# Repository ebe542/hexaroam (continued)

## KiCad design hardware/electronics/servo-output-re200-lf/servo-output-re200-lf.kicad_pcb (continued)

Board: 2 copper layers, 83 parts (0 on the bottom side), 38 nets, no tracks yet.

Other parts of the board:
BG0, BG1, BG2, BG3, BG4, BG5: GND; TestPoint_THTPad_D2.0mm_Drill1.0mm
BV0, BV1, BV2, BV3, BV4, BV5: /SERVO_VS; TestPoint_THTPad_D2.0mm_Drill1.0mm

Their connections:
/SERVO_VS: BV0.1, BV1.1, BV2.1, BV3.1, BV4.1, BV5.1; also elsewhere on the board
GND: BG0.1, BG1.1, BG2.1, BG3.1, BG4.1, BG5.1; also elsewhere on the board

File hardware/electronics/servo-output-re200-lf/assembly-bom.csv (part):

Reference,Quantity,Value,Population,Notes,Footprint
J101,1,SIGNAL INPUT,Fit first,"Keyed 2x6 IDC; odd signals, even GND; key notch toward small columns",Connector_IDC:IDC-Header_2x06_P2.54mm_Vertical
J102,1,SERVO POWER IN,Fit first,"Reference Phoenix 1715721, 5.08mm; enlarge two holes to 1.3mm; current sizing for six servos remains open","TerminalBlock_Phoenix:TerminalBlock_Phoenix_MKDS-1,5-2-5.08_1x02_P5.08mm_Horizontal"
C100,1,470uF / 35V,Fit first,"Existing: 470uF/35V, D10 x H20mm, leads 5.00mm gently formed to 5.08mm; observe polarity",HexaRoam_Perfboard:CP_Radial_D10.0mm_P5.08mm_HandFormed
TP101,1,SERVO 0 SIGNAL,Fit first,,TestPoint:TestPoint_THTPad_D2.0mm_Drill1.0mm
TP102,1,LOCAL GND,Fit first,,TestPoint:TestPoint_THTPad_D2.0mm_Drill1.0mm
R101,1,4.7k,Fit first,"Metal film >=0.25W, body fits DIN0207 6.3x2.5mm, P10.16mm",Resistor_THT:R_Axial_DIN0207_L6.3mm_D2.5mm_P10.16mm_Horizontal
R102,1,1k,Fit first,"Metal film >=0.25W, body fits DIN0207 6.3x2.5mm, P10.16mm",Resistor_THT:R_Axial_DIN0207_L6.3mm_D2.5mm_P10.16mm_Horizontal
R103,1,4.7k,Fit first,"Metal film >=0.25W, body fits DIN0207 6.3x2.5mm, P10.16mm",Resistor_THT:R_Axial_DIN0207_L6.3mm_D2.5mm_P10.16mm_Horizontal
R104,1,1k,Fit first,"Metal film >=0.25W, body fits DIN0207 6.3x2.5mm, P10.16mm",Resistor_THT:R_Axial_DIN0207_L6.3mm_D2.5mm_P10.16mm_Horizontal
R105,1,100k,Fit first,"Metal film >=0.25W, body fits DIN0207 6.3x2.5mm, P10.16mm",Resistor_THT:R_Axial_DIN0207_L6.3mm_D2.5mm_P10.16mm_Horizontal
R106,1,180,Fit first,"Metal film >=0.25W, body fits DIN0207 6.3x2.5mm, P10.16mm",Resistor_THT:R_Axial_DIN0207_L6.3mm_D2.5mm_P10.16mm_Horizontal
R107,1,100k,Fit first,"Metal film >=0.25W, body fits DIN0207 6.3x2.5mm, P10.16mm",Resistor_THT:R_Axial_DIN0207_L6.3mm_D2.5mm_P10.16mm_Horizontal
Q101,1,BC547B,Fit first,"Purchasing reference Diotec BC547B / Reichelt BC 547B DIO; 1=C,2=B,3=E; 2.54mm lead row; verify exact supplied package",Package_TO_SOT_THT:TO-92_Inline_Wide
Q102,1,BC547B,Fit first,"Purchasing reference Diotec BC547B / Reichelt BC 547B DIO; 1=C,2=B,3=E; 2.54mm lead row; verify exact supplied package",Package_TO_SOT_THT:TO-92_Inline_Wide
C101,1,100nF,Fit first,100nF ceramic reference envelope <=5x2.5mm; lead pitch formed to 2.54mm,HexaRoam_Perfboard:C_Disc_D5.0mm_P2.54mm_HandFormed
J110,1,SERVO 0,Fit first,1 signal / 2 positive / 3 GND; verify cable orientation,Connector_PinHeader_2.54mm:PinHeader_1x03_P2.54mm_Vertical
R111,1,4.7k,DNP / future,"Metal film >=0.25W, body fits DIN0207 6.3x2.5mm, P10.16mm",Resistor_THT:R_Axial_DIN0207_L6.3mm_D2.5mm_P10.16mm_Horizontal
R112,1,1k,DNP / future,"Metal film >=0.25W, body fits DIN0207 6.3x2.5mm, P10.16mm",Resistor_THT:R_Axial_DIN0207_L6.3mm_D2.5mm_P10.16mm_Horizontal
R113,1,4.7k,DNP / future,"Metal film >=0.25W, body fits DIN0207 6.3x2.5mm, P10.16mm",Resistor_THT:R_Axial_DIN0207_L6.3mm_D2.5mm_P10.16mm_Horizontal
R114,1,1k,DNP / future,"Metal film >=0.25W, body fits DIN0207 6.3x2.5mm, P10.16mm",Resistor_THT:R_Axial_DIN0207_L6.3mm_D2.5mm_P10.16mm_Horizontal
R115,1,100k,DNP / future,"Metal film >=0.25W, body fits DIN0207 6.3x2.5mm, P10.16mm",Resistor_THT:R_Axial_DIN0207_L6.3mm_D2.5mm_P10.16mm_Horizontal
R116,1,180,DNP / future,"Metal film >=0.25W, body fits DIN0207 6.3x2.5mm, P10.16mm",Resistor_THT:R_Axial_DIN0207_L6.3mm_D2.5mm_P10.16mm_Horizontal
R117,1,100k,DNP / future,"Metal film >=0.25W, body fits DIN0207 6.3x2.5mm, P10.16mm",Resistor_THT:R_Axial_DIN0207_L6.3mm_D2.5mm_P10.16mm_Horizontal
Q103,1,BC547B,DNP / future,"Purchasing reference Diotec BC547B / Reichelt BC 547B DIO; 1=C,2=B,3=E; 2.54mm lead row; verify exact supplied package",Package_TO_SOT_THT:TO-92_Inline_Wide
Q104,1,BC547B,DNP / future,"Purchasing reference Diotec BC547B / Reichelt BC 547B DIO; 1=C,2=B,3=E; 2.54mm lead row; verify exact supplied package",Package_TO_SOT_THT:TO-92_Inline_Wide
C102,1,100nF,DNP / future,100nF ceramic reference envelope <=5x2.5mm; lead pitch formed to 2.54mm,HexaRoam_Perfboard:C_Disc_D5.0mm_P2.54mm_HandFormed
J111,1,SERVO 1,DNP / future,1 signal / 2 positive / 3 GND; verify cable orientation,Connector_PinHeader_2.54mm:PinHeader_1x03_P2.54mm_Vertical
R121,1,4.7k,DNP / future,"Metal film >=0.25W, body fits DIN0207 6.3x2.5mm, P10.16mm",Resistor_THT:R_Axial_DIN0207_L6.3mm_D2.5mm_P10.16mm_Horizontal
R122,1,1k,DNP / future,"Metal film >=0.25W, body fits DIN0207 6.3x2.5mm, P10.16mm",Resistor_THT:R_Axial_DIN0207_L6.3mm_D2.5mm_P10.16mm_Horizontal
R123,1,4.7k,DNP / future,"Metal film >=0.25W, body fits DIN0207 6.3x2.5mm, P10.16mm",Resistor_THT:R_Axial_DIN0207_L6.3mm_D2.5mm_P10.16mm_Horizontal
R124,1,1k,DNP / future,"Metal film >=0.25W, body fits DIN0207 6.3x2.5mm, P10.16mm",Resistor_THT:R_Axial_DIN0207_L6.3mm_D2.5mm_P10.16mm_Horizontal
R125,1,100k,DNP / future,"Metal film >=0.25W, body fits DIN0207 6.3x2.5mm, P10.16mm",Resistor_THT:R_Axial_DIN0207_L6.3mm_D2.5mm_P10.16mm_Horizontal
R126,1,180,DNP / future,"Metal film >=0.25W, body fits DIN0207 6.3x2.5mm, P10.16mm",Resistor_THT:R_Axial_DIN0207_L6.3mm_D2.5mm_P10.16mm_Horizontal
R127,1,100k,DNP / future,"Metal film >=0.25W, body fits DIN0207 6.3x2.5mm, P10.16mm",Resistor_THT:R_Axial_DIN0207_L6.3mm_D2.5mm_P10.16mm_Horizontal
Q105,1,BC547B,DNP / future,"Purchasing reference Diotec BC547B / Reichelt BC 547B DIO; 1=C,2=B,3=E; 2.54mm lead row; verify exact supplied package",Package_TO_SOT_THT:TO-92_Inline_Wide
Q106,1,BC547B,DNP / future,"Purchasing reference Diotec BC547B / Reichelt BC 547B DIO; 1=C,2=B,3=E; 2.54mm lead row; verify exact supplied package",Package_TO_SOT_THT:TO-92_Inline_Wide
C103,1,100nF,DNP / future,100nF ceramic reference envelope <=5x2.5mm; lead pitch formed to 2.54mm,HexaRoam_Perfboard:C_Disc_D5.0mm_P2.54mm_HandFormed
J112,1,SERVO 2,DNP / future,1 signal / 2 positive / 3 GND; verify cable orientation,Connector_PinHeader_2.54mm:PinHeader_1x03_P2.54mm_Vertical
R131,1,4.7k,DNP / future,"Metal film >=0.25W, body fits DIN0207 6.3x2.5mm, P10.16mm",Resistor_THT:R_Axial_DIN0207_L6.3mm_D2.5mm_P10.16mm_Horizontal
R132,1,1k,DNP / future,"Metal film >=0.25W, body fits DIN0207 6.3x2.5mm, P10.16mm",Resistor_THT:R_Axial_DIN0207_L6.3mm_D2.5mm_P10.16mm_Horizontal
R133,1,4.7k,DNP / future,"Metal film >=0.25W, body fits DIN0207 6.3x2.5mm, P10.16mm",Resistor_THT:R_Axial_DIN0207_L6.3mm_D2.5mm_P10.16mm_Horizontal
R134,1,1k,DNP / future,"Metal film >=0.25W, body fits DIN0207 6.3x2.5mm, P10.16mm",Resistor_THT:R_Axial_DIN0207_L6.3mm_D2.5mm_P10.16mm_Horizontal
R135,1,100k,DNP / future,"Metal film >=0.25W, body fits DIN0207 6.3x2.5mm, P10.16mm",Resistor_THT:R_Axial_DIN0207_L6.3mm_D2.5mm_P10.16mm_Horizontal
R136,1,180,DNP / future,"Metal film >=0.25W, body fits DIN0207 6.3x2.5mm, P10.16mm",Resistor_THT:R_Axial_DIN0207_L6.3mm_D2.5mm_P10.16mm_Horizontal
R137,1,100k,DNP / future,"Metal film >=0.25W, body fits DIN0207 6.3x2.5mm, P10.16mm",Resistor_THT:R_Axial_DIN0207_L6.3mm_D2.5mm_P10.16mm_Horizontal
Q107,1,BC547B,DNP / future,"Purchasing reference Diotec BC547B / Reichelt BC 547B DIO; 1=C,2=B,3=E; 2.54mm lead row; verify exact supplied package",Package_TO_SOT_THT:TO-92_Inline_Wide
Q108,1,BC547B,DNP / future,"Purchasing reference Diotec BC547B / Reichelt BC 547B DIO; 1=C,2=B,3=E; 2.54mm lead row; verify exact supplied package",Package_TO_SOT_THT:TO-92_Inline_Wide
C104,1,100nF,DNP / future,100nF ceramic reference envelope <=5x2.5mm; lead pitch formed to 2.54mm,HexaRoam_Perfboard:C_Disc_D5.0mm_P2.54mm_HandFormed
J113,1,SERVO 3,DNP / future,1 signal / 2 positive / 3 GND; verify cable orientation,Connector_PinHeader_2.54mm:PinHeader_1x03_P2.54mm_Vertical
R141,1,4.7k,DNP / future,"Metal film >=0.25W, body fits DIN0207 6.3x2.5mm, P10.16mm",Resistor_THT:R_Axial_DIN0207_L6.3mm_D2.5mm_P10.16mm_Horizontal
R142,1,1k,DNP / future,"Metal film >=0.25W, body fits DIN0207 6.3x2.5mm, P10.16mm",Resistor_THT:R_Axial_DIN0207_L6.3mm_D2.5mm_P10.16mm_Horizontal
R143,1,4.7k,DNP / future,"Metal film >=0.25W, body fits DIN0207 6.3x2.5mm, P10.16mm",Resistor_THT:R_Axial_DIN0207_L6.3mm_D2.5mm_P10.16mm_Horizontal
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
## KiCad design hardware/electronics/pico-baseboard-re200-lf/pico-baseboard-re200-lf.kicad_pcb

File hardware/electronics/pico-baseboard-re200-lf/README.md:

# Pico baseboard on Roth RE200-LF

Revision P1, 2026-10-27: unbuilt placement and hand-wiring proposal for the controller assembly of the [revision C schematic](../pico-servo-system/README.md). This folder contains the Pico baseboard only, not the servo-output module or motor supply.

## Files

- [KiCad board](pico-baseboard-re200-lf.kicad_pcb) and [project](pico-baseboard-re200-lf.kicad_pro).
- [Seven-page assembly PDF](assembly-guide.pdf), A4 landscape, drawn at 1:1.
- [Component-side SVG](placement-top.svg) and [mirrored solder-side SVG](placement-bottom.svg).
- Solder-side wire groups: [ground/power](wiring-ground-power.svg), [port A](wiring-port-a.svg), [port B](wiring-port-b.svg), [port C](wiring-port-c.svg), [UART/expansion](wiring-other.svg). Hover a wire in a browser to highlight it and display its ID/net.
- [Complete wire endpoint list](wiring.csv), [physical pin map](pin-map.csv), [assembly parts](assembly-bom.csv).
- [Layout model](layout-model.json) and [verification record](layout-check.json).

The PDF, SVG and CSV files are a snapshot of the same model as the KiCad board. Moving a footprint in KiCad does not automatically update these documents. Reconcile all views and rerun the connection/geometry review before using a changed layout. Recorded hashes identify the checked snapshot.

## Board, coordinate system and views

Use the existing RE200-LF: FR4, 1.5-mm thickness, single-sided solder pads, 61 columns x 38 rows, 2.54-mm pitch, 2.2-mm pad diameter and nominal 1.0-mm holes. The manufacturer calls it 100 x 160 mm; its drawing dimensions are 160.15 x 100.20 mm. The illustrated first hole is modeled at x=3.89, y=3.07 mm from the drawing's top-left corner. Check actual board tolerances and orientation before relying on edge registration.

All IDs are defined looking at the COMPONENT side, with the copper underneath and the Pico USB facing left:

```text
C01-R01 = first column, first row (top left)
x = 3.89 + (column - 1) * 2.54 mm
y = 3.07 + (row - 1) * 2.54 mm
```

These are our coordinate labels, not a promise that the manufacturer's printed numbering has the same viewing orientation. In the solder-side drawings the board is flipped horizontally, like turning a page: USB is on the right, row 1 remains at the top, column 61 is on the left. Physical hole IDs never change. Do not mirror an already mirrored solder-side PDF again.

Print at Actual size / 100%, with all Fit/Shrink options disabled. Measure the 50-mm scale bar and align three widely separated existing holes with the paper before assembly. The PDF is not an instruction to drill all the existing holes.

## Placement and polarity

| Item | Physical position / orientation |
| --- | --- |
| U1 lower socket | C01..C20, R21; Pico pins 1..20 from left to right |
| U1 upper socket | C01..C20, R14; Pico pins 40..21 from left to right |
| Socket row separation | 17.78 mm; two individual 1x20 female headers |
| J1 | Pin 1 positive: C12-R04; pin 2 GND: C10-R04 |
| D2 | 1N5819 cathode/band (pin 1): C16-R08; anode (pin 2): C20-R08 |
| J2 port A | Pin 1 C53-R04; GP0..GP5 on odd pins; even pins GND |
| J3 port B | Pin 1 C53-R15; GP6..GP11 on odd pins; even pins GND |
| J4 port C | Pin 1 C53-R26; GP12..GP17 on odd pins; even pins GND |
| IDC key notches | Face toward the Pico/odd-pin side, left in component view, right in solder view |
| J5 UART | Pins 1..3 C06..C08, R32: TX / RX / GND; 3.3-V TTL |
| J6 expansion | Pins 1..8 C24..C31, R33: GP18, GP19, GP22, GP26, GP27, GP28, 3V3, GND |
| TP1 / TP2 | VSYS: C24-R06 / USB VBUS: C24-R10 |
| TP3 / TP4 / TP5 | GP0: C03-R26 / GP1: C07-R26 / GND: C12-R26 |

Confirm the molded pin-1 mark and key of the actual IDC connectors; pin numbers, not drawing resemblance, define the wiring. Standard footprint body dimensions are reference envelopes. The actual sockets, IDC cable plugs/latches and terminal must fit without contacting the Pico or neighboring parts. Preserve access above USB, BOOTSEL and the Pico SWD pads.

## Mechanical changes on the existing board

The reference J1 is a Phoenix MKDS 1,5/2-5,08 style footprint, 5.08-mm pitch. Its 0.9-mm square pins require 1.3-mm holes. ONLY its two occupied holes, C12-R04 and C10-R04, need widening for this reference part. Remove burrs, inspect the remaining pad rings and support the terminal body when tightening wires. A different terminal needs a fresh pin-size/body check; 5.00-mm pitch is not 5.08 mm. The matching reference part is Phoenix Contact 1715721, listed at Reichelt as MKDS 1,5 2 5,08. A different seller's compatible part still needs a dimension check.

D2 uses the existing 1.0-mm perfboard holes in this layout; verify that the delivered diode leads fit freely. The generic manufacturing footprint's larger drill allowance is not a requirement to force or automatically re-drill the board.

Optional M3 mounting reserves are C03-R03, C59-R03, C03-R36 and C59-R36. Circles show 3.2-mm holes and a 4-mm-radius keep-clear area; they are drawing guides, not existing holes. Decide spacer/washer arrangement and drill only if needed. Keep all nearby pads unused, inspect for damaged copper and leave wiring clear of mounting hardware. The schematic does not determine chassis-hole requirements.

## Hand wiring

All 61 entries in wiring.csv are separate insulated-wire connections. Each row gives component pin and physical hole at both ends. straight_mm is the geometric endpoint distance; cut_hint_mm is that distance plus approximately 20 mm, rounded up, not a measured routed length. Select a practical path and provide enough slack without obstructing sockets or mounting points.

Lines crossing in the SVG/PDF or Cmts.User layer do NOT form junctions. Do not reproduce crossings using bare wire. Only the named endpoints are electrically joined. Solder wire ends to the rear pad/component tail rather than attempting to push several wires through a hole already occupied by a connector pin. No pad has more than three wire ends in the proposed tree; check the real joint can be made cleanly and supported.

Use appropriately sized insulated hookup wire and protect it from sharp leads; keep power/ground mechanically secure. Each IDC's six ground pins are connected. The board carries Pico power and logic only: NO servo-positive rail or motor return current runs through it.

The exported KiCad 10 schematic includes all seven physical Pico GND pins (3, 8, 13, 18, 23, 28, 38). All seven are wired to the common baseboard ground, so the ground network is complete even with the Pico removed. AGND/pin 33, RUN, ADC_VREF and 3V3_EN are not externally wired. Grey pads identify the unused pins.

## Using the KiCad board

Open the .kicad_pcb directly, or use the separate project. The original three-sheet schematic models three physical assemblies, so do not blindly run Update PCB from Schematic from that full system into this controller-only board. There is no duplicated schematic in this folder.

- F.Fab / F.SilkS show component bodies/reference marks.
- Dwgs.User shows the existing perfboard grid, coordinates and optional mounting reserves.
- Cmts.User shows endpoint guide segments for insulated wires. Hide it for a clean placement view.
- There are NO copper tracks or routed jumpers. Ratsnest/unconnected indications are expected until physical hand wiring; this is not a claim of passing production PCB DRC.

KiCad represents the electrical through-hole component pads using a standard THT model with rings on both copper layers. Those front rings are virtual for this guide. The real RE200-LF is single-sided and not plated through. The thousands of unused solder pads/holes are drawing geometry, not a complete fabrication stackup. Do not order PCBs or drill files from this template. Its purpose is editable placement and hand-wiring documentation for an already manufactured board.

The local HexaRoam_Perfboard.pretty footprint retains only the 40 main THT pads of the standard Pico module footprint; SMD/castellation and Pico-local mechanical/SWD pads are not carrier socket holes. It models two 1x20 sockets rather than soldering the Pico directly to the baseboard. Its pin numbering matches the Pico module.

## Verification and owner-performed assembly checks

The saved KiCad board was independently reloaded and checked against the fresh revision C schematic netlist: 13 components, 96 physical pins and 61 wires. Every source root-sheet pin maps to exactly one physical hole. All occupied pads lie on the declared grid without overlap, the component envelope rectangles are separated and inside the board, and every connected net has a complete, non-shorting wire tree. Source/export hashes are in layout-check.json. This is document/geometry verification, not firmware testing or a hardware pass.

Suggested manual sequence for the owner:

1. Print at 100% and check registration; dry-fit sockets, diode and connectors. Check polarity/keying. Decide the terminal/mounting drilling before fitting parts.
2. Fit and solder sockets with the Pico removed. Solder the other parts, then work through the ground/power, A, B, C and other wire tables. Keep a paper checklist per wire.
3. With no power, Pico or external cables attached, check every listed connection and inspect for solder bridges. Verify separate positive nets: external +5V reaches only D2 anode; D2 cathode reaches VSYS; VBUS is not wired directly to either positive net. Use diode mode for D2; capacitor/semiconductor behavior after fitting Pico changes simple resistance readings.
4. Check supply polarity and ground arrangement with the existing USB/UART equipment. Insert the Pico only after inspecting the bare baseboard. Bring up external Pico power and verify VSYS; then repeat the established blink/UART/unloaded-signal checks. Servo power remains on the separate power/output assemblies.

## Reference documents and licensing

- [Roth RE200-LF manufacturer drawing, 072025](https://www.roth-elektronik.com/pdf/en_RE200-LF.pdf). An unmodified local copy and its source/hash are archived under ignored local-data/perfboard/; third-party terms apply.
- [Pico datasheet](../../references/raspberry-pi-pico/pico-datasheet.pdf), mechanical dimensions and external VSYS supply.
- [Reference terminal dimensions](https://www.phoenixcontact.com/gb/products/1715721/pdf): MKDS 1,5/2-5,08, 5.08-mm pitch, 0.9x0.9-mm pins, 1.3-mm holes.
- [Reichelt reference terminal listing](https://www.reichelt.com/de/en/shop/product/pcb_terminal_2-pin_spacing_5_08_mm_0_14_-_1_5_mm_-440491), checked 2026-10-27. Manufacturer/distributor PDF downloads returned HTTP 403 during local archiving; the primary dimensions and source links are recorded here and under local-data/perfboard/reference-terminal-notes.md. The Roth board PDF is archived locally.
- Standard footprint geometry comes from the installed KiCad 10.0 libraries. The socketed Pico derivative retains the [KiCad Libraries License and electronic-design exception](https://gitlab.com/kicad/libraries/kicad-footprints/-/blob/master/LICENSE.md). Project-specific placement, wire data and explanatory documents are HexaRoam material under the repository MIT license; upstream footprint and datasheet rights remain separate.

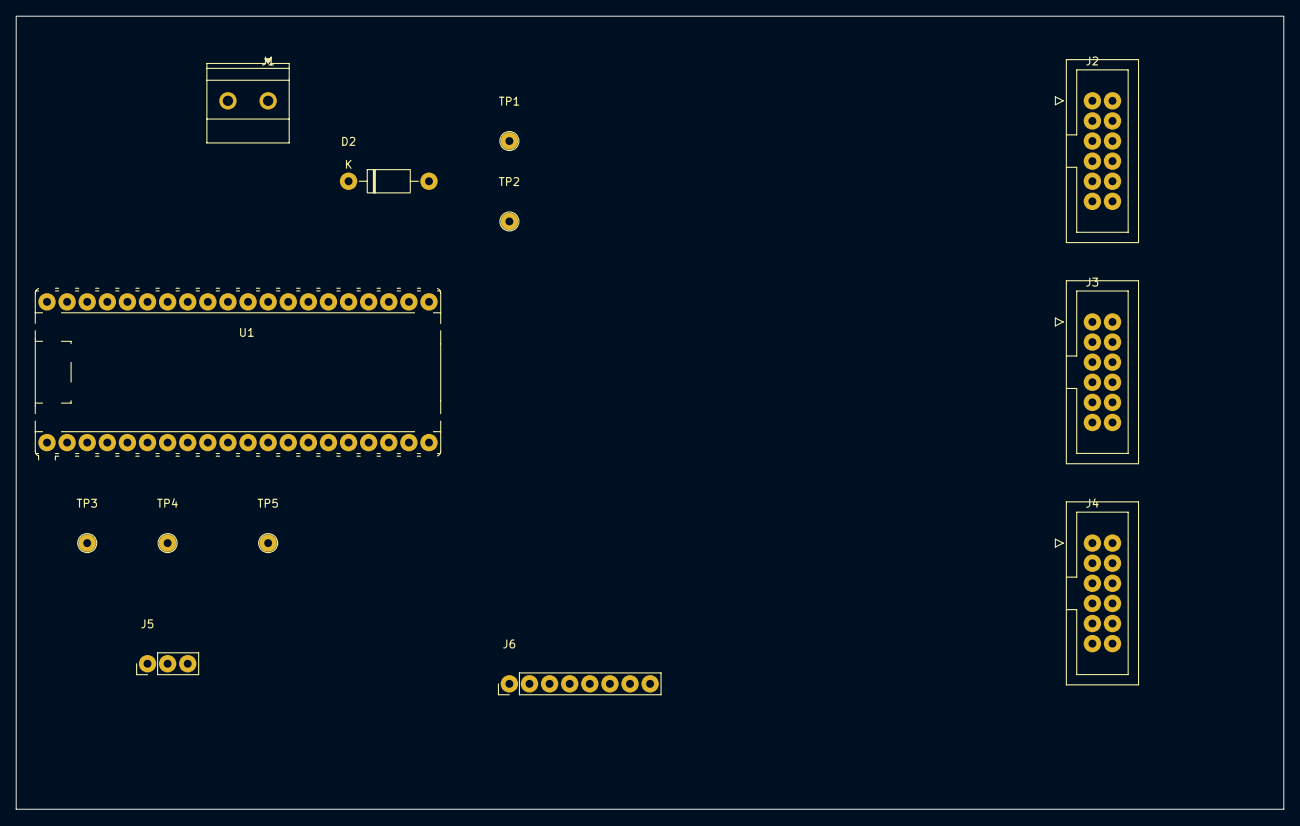
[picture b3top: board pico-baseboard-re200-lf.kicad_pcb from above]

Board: 2 copper layers, 160.2 x 100.2 mm, 13 parts (0 on the bottom side), 31 nets, no tracks yet.

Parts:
D2: 1N5819; D_DO-41_SOD81_P10.16mm_Horizontal
J1: PICO 5V IN; TerminalBlock_Phoenix_MKDS-1,5-2-5.08_1x02_P5.08mm_Horizont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
J2: PORT A: 0..5; IDC-Header_2x06_P2.54mm_Vertical
J3: PORT B: 6..11; IDC-Header_2x06_P2.54mm_Vertical
J4: PORT C: 12..17; IDC-Header_2x06_P2.54mm_Vertical
J5: UART 3V3 TTL; PinHeader_1x03_P2.54mm_Vertical
J6: EXPANSION; PinHeader_1x08_P2.54mm_Vertical
TP1: VSYS; TestPoint_THTPad_D2.0mm_Drill1.0mm
TP2: USB VBUS; TestPoint_THTPad_D2.0mm_Drill1.0mm
TP3: GP0; TestPoint_THTPad_D2.0mm_Drill1.0mm
TP4: GP1; TestPoint_THTPad_D2.0mm_Drill1.0mm
TP5: GND; TestPoint_THTPad_D2.0mm_Drill1.0mm
U1: Raspberry Pi Pico; Pico_Socketed_RE200

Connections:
/GP18: J6.1, U1.24
/GP19: J6.2, U1.25
/GP22: J6.3, U1.29
/GP26: J6.4, U1.31
/GP27: J6.5, U1.32
/GP28: J6.6, U1.34
/PICO_3V3: J6.7, U1.36
/PICO_EXT_5V: D2.2, J1.1
/PICO_VSYS: D2.1, TP1.1, U1.39
/SERVO0_3V3: J2.1, TP3.1, U1.1
/SERVO1_3V3: J2.3, TP4.1, U1.2
/SERVO2_3V3: J2.5, U1.4
/SERVO3_3V3: J2.7, U1.5
/SERVO4_3V3: J2.9, U1.6
/SERVO5_3V3: J2.11, U1.7
/SERVO6_3V3: J3.1, U1.9
/SERVO7_3V3: J3.3, U1.10
/SERVO8_3V3: J3.5, U1.11
/SERVO9_3V3: J3.7, U1.12
/SERVO10_3V3: J3.9, U1.14
/SERVO11_3V3: J3.11, U1.15
/SERVO12_3V3: J4.1, U1.16
/SERVO13_3V3: J4.3, U1.17
/SERVO14_3V3: J4.5, U1.19
/SERVO15_3V3: J4.7, U1.20
/SERVO16_3V3: J4.9, U1.21
/SERVO17_3V3: J4.11, U1.22
/UART1_RX: J5.2, U1.27
/UART1_TX: J5.1, U1.26
/USB_VBUS: TP2.1, U1.40
GND: J1.2, J2.2, J2.4, J2.6, J2.8, J2.10, J2.12, J3.2, J3.4, J3.6, J3.8, J3.10, J3.12, J4.2, J4.4, J4.6, J4.8, J4.10, J4.12, J5.3, J6.8, TP5.1, U1.3, U1.8, U1.13, U1.18, U1.23, U1.28, U1.38
